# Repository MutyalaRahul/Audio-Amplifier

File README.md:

# Audio-Amplifier
Simple Audio Amplifier/Detector PCB design using KiCad8.

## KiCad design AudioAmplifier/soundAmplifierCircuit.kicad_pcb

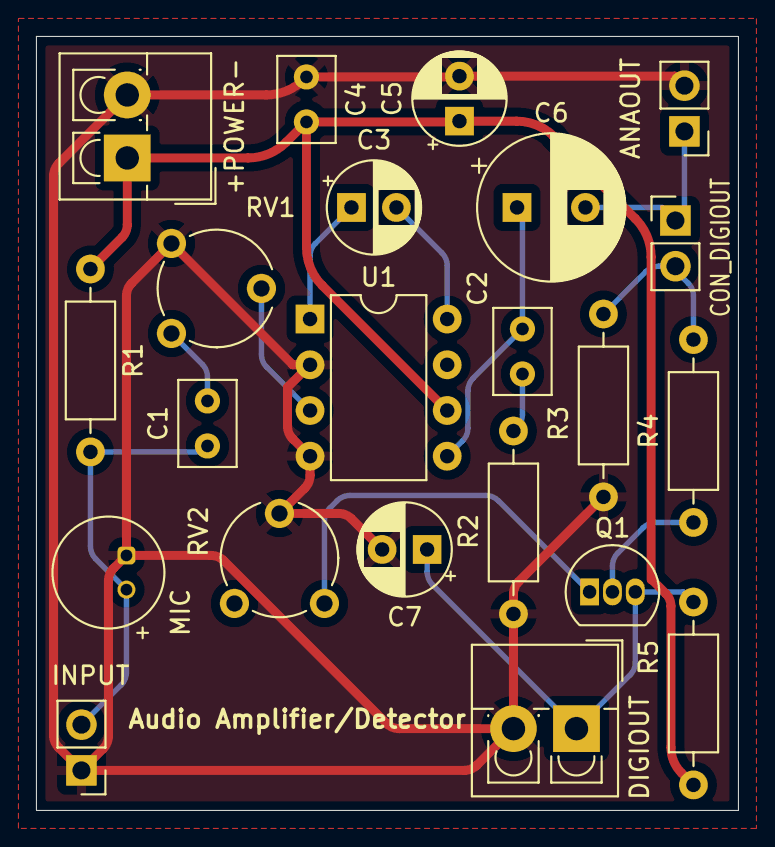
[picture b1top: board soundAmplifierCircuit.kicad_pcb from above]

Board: 2 copper layers, 39.0 x 43.0 mm, 22 parts (0 on the bottom side), 14 nets.

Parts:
+POWER-: TerminalBlock_4Ucon_1x02_P3.50mm_Vertical
ANAOUT: PinHeader_1x02_P2.54mm_Vertical
C1, C4: 100n; C_Rect_L4.6mm_W3.0mm_P2.50mm_MKS02_FKP02
C2: 200n; C_Rect_L4.6mm_W3.0mm_P2.50mm_MKS02_FKP02
C3: 10u; CP_Radial_D5.0mm_P2.50mm
C5: 33u; CP_Radial_D5.0mm_P2.50mm
C6: 470u; CP_Radial_D8.0mm_P3.80mm
C7: 4.7u; CP_Radial_D5.0mm_P2.50mm
CON_DIGIOUT: PinHeader_1x02_P2.54mm_Vertical
DIGIOUT: TerminalBlock_4Ucon_1x02_P3.50mm_Vertical
INPUT: PinHeader_1x02_P2.54mm_Vertical
MIC: POM-2244P-C3310-2-R
Q1: PN2222A; TO-92_Inline
R1, R4, R5: 10k; R_Axial_DIN0207_L6.3mm_D2.5mm_P10.16mm_Horizontal
R2, R3: 10; R_Axial_DIN0207_L6.3mm_D2.5mm_P10.16mm_Horizontal
RV1: 10k; Potentiometer_Piher_PT-6-V_Vertical
RV2: 1k; Potentiometer_Piher_PT-6-V_Vertical
U1: LM386; DIP-8_W7.62mm

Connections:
+5V: +POWER-.1, C4.2, C5.1, R1.1, R5.2, U1.6 (V+)
GND: +POWER-.2, ANAOUT.2, C4.1, C5.2, C7.2, DIGIOUT.2, INPUT.1, MIC.1 (-), R2.2, R3.2, RV1.3, RV2.2, U1.2 (-), U1.4 (GND)
unnamed: ANAOUT.1, C6.2, CON_DIGIOUT.1
unnamed: C1.2, RV1.1
unnamed: C2.1, R2.1
unnamed: C2.2, C6.1, U1.5
unnamed: C3.1, U1.1 (GAIN)
unnamed: C3.2, U1.8 (GAIN)
unnamed: C7.1, DIGIOUT.1, Q1.3 (C), R5.1
unnamed: C1.1, INPUT.2, MIC.2 (+), R1.2
unnamed: CON_DIGIOUT.2, R3.1, R4.1
unnamed: Q1.2 (B), R4.2
unnamed: Q1.1 (E), RV2.1
unnamed: RV1.2, U1.3 (+)

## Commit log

2025-10-17 Add files via upload
    Designed a Audio Amplifier PCB layout using KiCad software
